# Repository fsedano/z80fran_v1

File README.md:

# Home brew Z80 computer

Nothing unusual or special. But I learnt coding on a ZX Spectrum back in 1981.. So now, older and wiser (?) why not recreating (yet another) Z80 computer just because?

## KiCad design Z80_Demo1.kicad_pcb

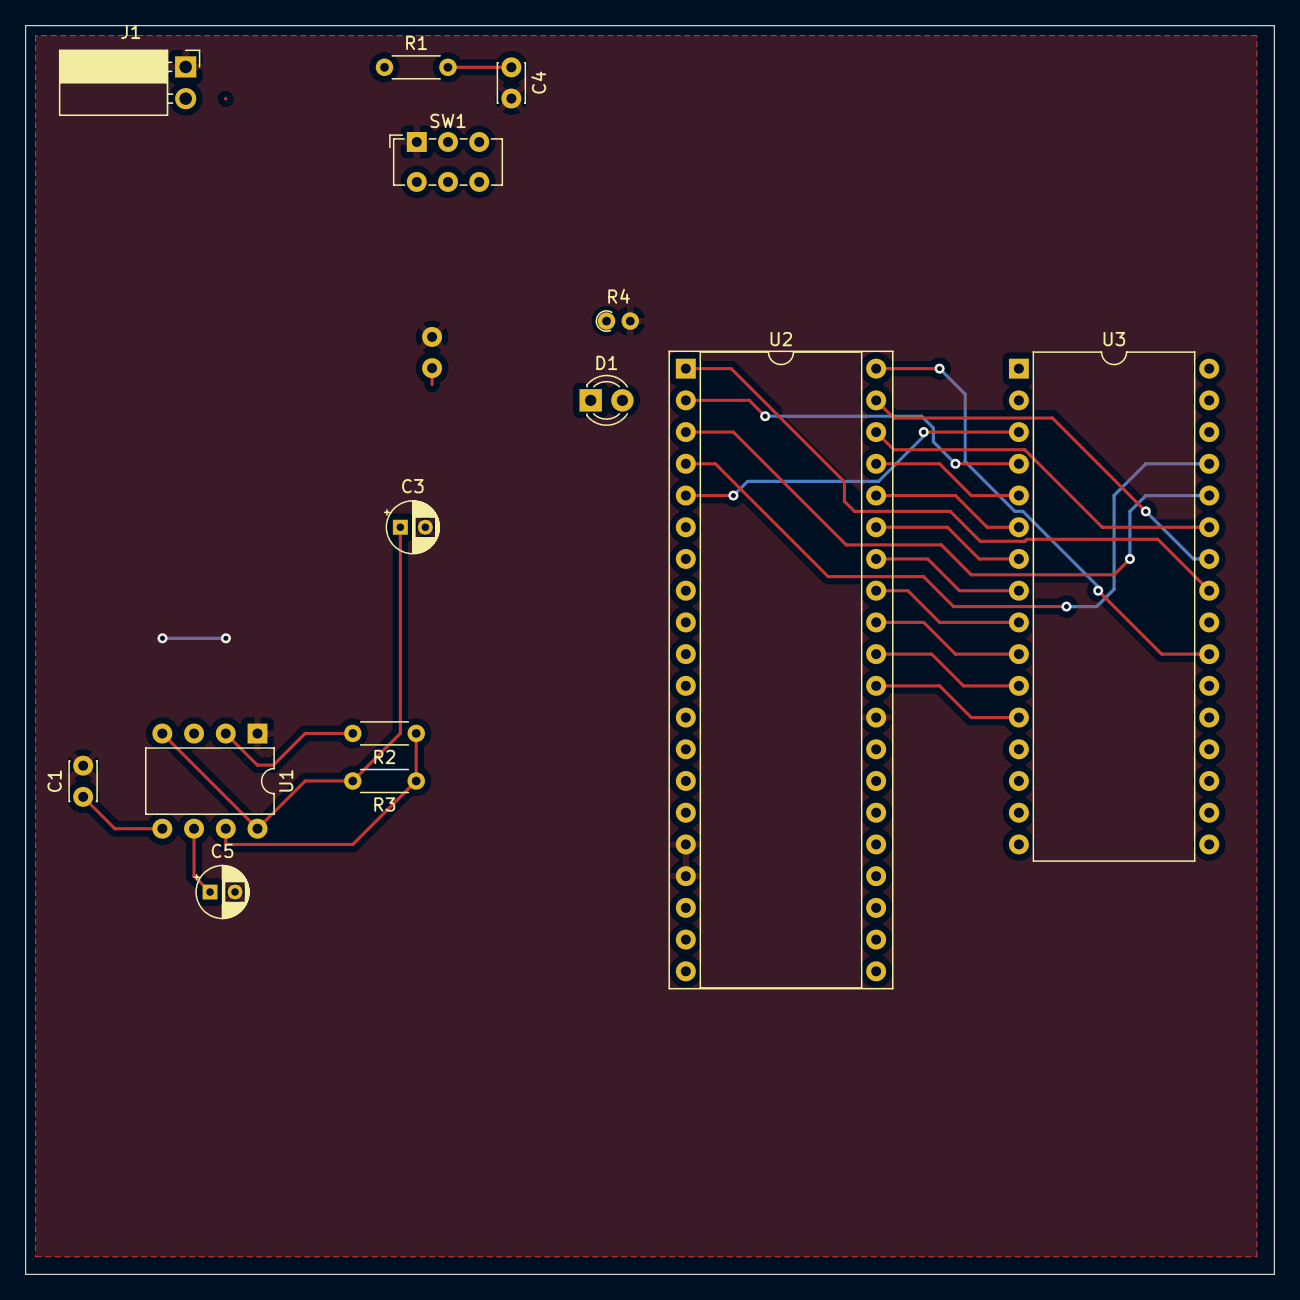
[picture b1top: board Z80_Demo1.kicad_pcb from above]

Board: 2 copper layers, 100.0 x 100.0 mm, 15 parts (1 on the bottom side), 24 nets.

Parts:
C1: 10n; C_Disc_D3.0mm_W2.0mm_P2.50mm
C2, C4: 100nF; C_Disc_D3.0mm_W2.0mm_P2.50mm
C3, C5: 10u; CP_Radial_D4.0mm_P2.00mm
D1: LED; LED_D3.0mm
J1: Conn_01x02_Pin; PinSocket_1x02_P2.54mm_Horizontal
R1: R; R_Axial_DIN0204_L3.6mm_D1.6mm_P5.08mm_Horizontal
R2: 4k7; R_Axial_DIN0204_L3.6mm_D1.6mm_P5.08mm_Horizontal
R3: 1k; R_Axial_DIN0204_L3.6mm_D1.6mm_P5.08mm_Horizontal
R4: 470; R_Axial_DIN0204_L3.6mm_D1.6mm_P1.90mm_Vertical
SW1: SW_Push; SW_E-Switch_EG1271_SPDT
U1: NE555P; DIP-8_W7.62mm
U2: Z80CPU; DIP-40_W15.24mm_Socket
U3: SST39SF010; DIP-32_W15.24mm

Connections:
+5V: C2.2, C3.1, J1.2, R1.1, R3.2, U1.4 (R), U1.8 (VCC), U2.11 (VCC)
/A0: U2.30 (A0), U3.12 (A0)
/A1: U2.31 (A1), U3.11 (A1)
/A2: U2.32 (A2), U3.10 (A2)
/A3: U2.33 (A3), U3.9 (A3)
/A4: U2.34 (A4), U3.8 (A4)
/A5: U2.35 (A5), U3.7 (A5)
/A6: U2.36 (A6), U3.6 (A6)
/A7: U2.37 (A7), U3.5 (A7)
/A8: U2.38 (A8), U3.27 (A8)
/A9: U2.39 (A9), U3.26 (A9)
/A10: U2.40 (A10), U3.23 (A10)
/A11: U2.1 (A11), U3.25 (A11)
/A12: U2.2 (A12), U3.4 (A12)
/A13: U2.3 (A13), U3.28 (A13)
/A14: U2.4 (A14), U3.29 (A14)
/A15: U2.5 (A15), U3.3 (A15)
CLK: D1.2 (A), U1.3 (Q), U2.6 (~CLK)
GND: C1.2, C2.1, C3.2, C4.2, C5.2, J1.1, R4.2, SW1.1, U1.1 (GND), U2.16 (~INT), U2.17 (~NMI), U2.29 (GND)
unnamed: D1.1 (K), R4.1
unnamed: C1.1, U1.5 (CV)
unnamed: R2.1, R3.1, U1.7 (DIS)
unnamed: C5.1, R2.2, U1.2 (TR), U1.6 (THR)
unnamed: C4.1, R1.2, SW1.2, U2.26 (~RESET)

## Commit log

2023-11-27 Initial
2023-11-27 Add README
